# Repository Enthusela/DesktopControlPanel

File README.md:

# The Desktop Control Panel Project

An open-source, hand-built, tactile, home-brew smart-home hub with analog PC audio monitoring and control.

## Features

* ARGB LED device control with HSV and color-temperature control modes
* App-based volume mixing in Windows, including OS/Game/Discord channels
* Motorised knobs enable multiple control modes on a single set of inputs
* Mains power control: Toggle switches control mains power to the PC, monitors, and speakers via rental-safe RF-based remote-control mains outlets.
* Analog audio monitoring: PC soundcard connects to VU meters and IN-9 Nixie Tubes for level and 3-band spectrum monitoring, respectively
* Moog-inspired build quality: wood cabinet, black brushed-aluminium faceplate, big, satisfying switchgear, and actual Moog knobs/rockers because why not.
* "Seamless" E-ink display: White-on-black E-ink panel creates a non-light-emitting display integrated into the non-light-emitting faceplate.
* Integrated website: the website for this Control Panel project is hosted on the Raspberry Pi running inside the Control Panel
* Integration with Home Assistant for ARGB room-lighting via ESP Wifi boards
* Automatic Temperature-based color control: automatically transition room lighting from cool to warm as the sun sets here in Perth, Western Australia.
* Homebrew phone-control app: Home Assistant has this, of course, but this sounded like a good excuse to learn React Native.

<details>
<summary>Feature Development Status Table</summary>

| Feature/Pipeline                      | Order In Pipeline | Sub-function                        | Status |
|:--------------------------------------|:---:|:----------------------------------------------------|:-----|
| Faceplate -> Mega Hardware Pipeline   | 1   | Faceplate Input Hardware                            | Done |
| Faceplate -> Mega Hardware Pipeline   | 2   | Faceplate Input Breakout Board                      | Testing |
| Faceplate -> Mega Hardware Pipeline   | 3   | Mega* Input Shield                                  | Testing |
| Mega -> Raspi Hardware Pipeline       | 1   | USB Connection                                      | Done |
| Raspi -> Uno Hardware Pipeline        | 1   | USB Connection                                      | Done |
| Raspi -> PC Hardware Pipeline         | 1   | Local Wifi Connection                               | Done |
| Input Knob Motorisation               | 1   | Mega Programming - Input Knob Control Modes         | Done |
| Input Knob Motorisation               | 2   | Motor Driver Shield                                 | Done |
| Input Knob Motorisation               | 3   | Shield -> Motor Connection                          | Done | 
| PC ARGB Control                       | 1   | Mega Programming - Input signal processing          | Done |
| PC ARGB Control                       | 2a  | Raspi* Programming - Input passthrough to Uno       | Done |
| PC ARGB Control                       | 2b  | Raspi Programming - Home Assistant/Web App          | Not Started |
| PC ARGB Control                       | 3a  | Uno* Programming - Manual HSV-based Color Control   | Done |
| PC ARGB Control                       | 3b  | Uno Programming - Manual Temp-based Color Control   | Done |
| PC ARGB Control                       | 3c  | Uno Programming - Auto Temp-based Color Control     | Not Started |
| PC ARGB Control                       | 4   | Uno ARGB Breakout Shield                            | To Be Ordered |
| PC ARGB Control                       | 5   | PC ARGB Devices                                     | Done |
| PC Volume Control                     | 1   | Raspi Programming - Input passthrough to PC         | Done |
| PC Volume Control                     | 2a  | PC Programming - Main Volume Control                | Done |
| PC Volume Control                     | 2b  | PC Programming - Three-channel App Volume Control   | Done |
| PC Volume Control                     | 2c  | PC Programming - Audio Output Device Selection      | Done |
| Mains Power Control                   | 1   | Mega Programming - Input Signal Processing          | In progress |
| Mains Power Control                   | 2   | Mega -> RF PCB Breakout Board                       | In progress |
| Mains Power Control                   | 3   | RF PCB -> Remote Mains Outlet Connection            | In progress |
| Mains Power Control                   | 4   | Remote Mains Outlets - Test Working                 | In progress |
| PC Audio Level Meters                 | 1   | Soundcard TRS Output Levels                         | Done |
| PC Audio Level Meters                 | 2a  | Soundcard -> Driver Board Connection                | Done |
| PC Audio Level Meters                 | 2b  | Power Supply -> Driver Board Connection             | Developing |
| PC Audio Level Meters                 | 3   | VU Meter Driver Board                               | Done |
| PC Audio Level Meters                 | 4a  | VU Meter Level Outputs                              | Done |
| PC Audio Level Meters                 | 4b  | VU Meter LED Outputs                                | Done |
| PC Audio Level Meters                 | 5a  | VU Meters                                           | Done |
| PC Audio Level Meters                 | 5b  | VU Meter LEDs                                       | Prototyped |
| PC Audio Spectrum Analyser            | 1   | Soundcard Optical Output Levels                     | Done |
| PC Audio Spectrum Analyser            | 2   | Soundcard -> Digital I/O Board Connection           | Done |
| PC Audio Spectrum Analyser            | 3   | Raspberry Pi Digital Audio I/O Board                | Testing |
| PC Audio Spectrum Analyser            | 4   | Raspberry Pi Digital Audio I/O Processing           | Developing |
| PC Audio Spectrum Analyser            | 5   | Custom Nixie Tube Driver HAT                        | Developing |
| PC Audio Spectrum Analyser            | 6   | Driver HAT -> Nixie Tube Connection                 | Done |
| PC Audio Spectrum Analyser            | 7   | Power Supply to Driver Board                        | Developing |
| e-Ink Display                         | 1   | Raspberry Pi Programming - Image Output             | Developing |
| e-Ink Display                         | 2   | Raspberry Pi HAT                                    | Done |
| e-Ink Display                         | 3   | e-Ink Display                                       | Done |
| Project Website                       | 1   | Proxy Server (nginx)                                | Done |
| Project Website                       | 2   | Domain Hosting                                      | Done |
| Project Website                       | 3   | Server (node.js)                                    | Done |
| Project Website                       | 4a  | Homepage                                            | In progress |
| Project Website                       | 4b  | Brief                                               | In progress |
| Project Website                       | 4c  | Timeline                                            | In progress |
| Project Website                       | 4d  | Parts List                                          | In progress |
| Project Website                       | 4e  | Gallery                                             | In progress |
| Project Website                       | 4f  | Interactive Panel Map                               | Not started |
| Cabinet                               | N/A | Faceplate VU Meter Mounts                           | Done |
| Cabinet                               | N/A | Faceplate Nixie Tube Mounts                         | Done |
| Cabinet                               | N/A | Faceplate Soundcard Mount                           | Done |
| Cabinet                               | N/A | Faceplate e-Ink Display Mount                       | Done |
| Cabinet                               | N/A | Faceplate Input Knobs                               | Done |
| Cabinet                               | N/A | Faceplate Input Knob Motors/Gears                   | Done |
| Cabinet                               | N/A | Faceplate Input Rocker Switches                     | Done |
| Cabinet                               | N/A | Faceplate Input Toggle Switches                     | Done |
| Cabinet                               | N/A | Faceplate Input Push-button Switches                | Done |
| Cabinet                               | N/A | Internal Mounting Plate                             | Done |
| Cabinet                               | N/A | Rear Plate Plate                                    | Done |
| Cabinet                               | N/A | Cabinet Top Plate                                   | Done |
| Cabinet                               | N/A | Cabinet Side Plates                                 | Done |
| Cabinet                               | N/A | Cabinet Bottom Plate                                | In progress |
| Room ARGB Control                     | 1a  | Raspi Programming - Home Assistant Server           | Not started |
| Room ARGB Control                     | 1b  | Raspi Programming - Home Assistant Phone App        | Not started |
| Room ARGB Control                     | 2   | ESP32 Programming - Home Assistant Client           | Not started |
| Room ARGB Control                     | 3   | ESP32 ARGB Breakout Shield                          | Prototyped  |
| Room ARGB Control                     | 4   | Room ARGB Devices - Confirm Working                 | Not started |
| e-Ink Touch Overlay                   | 1   | Touch Overlay                                       | Not started |
| e-Ink Touch Overlay                   | 2   | Touch Overlay -> Raspi Connection                   | Not started |

* "Mega", "Raspi", and "Uno" refer to the Arduino Mega, Raspberry Pi, and Arduino Uno boards used, respectively.

</details>

## Background

This project grew out of a number of frustrations I was having building a killer PC setup that was both functional and aesthetically-pleasing: both important in a 1-by-1 apartment where said PC setup takes up a good third of the available living-room space.

<details>
<summary>ARGB controller software is not pleasant to use</summary>
<br>
The main idea for this project came out of my own frustration with existing hardware/software for controlling ARGB LEDs built into PC components. Most ARGB devices, like fans, must be plugged into a controller that interfaces with software running on the PC. This software is manufacturer-specific, closed-source, and typically quite limited in what it can do: you get some pre-loaded color patterns, but if you want it to do anything else, you're out of luck. To make matters worse, the software is often classic "bloatware": it insists on starting on login, then runs slow, chews up computer resources on functions you didn't ask for, and crashes often. Factor in multiple apps running for different manufacturers, and the user experience gets frustrating fast. While there is some scope to synchronise lighting across different manufacturer's products, these aren't ideal either: I was able to sync my CoolerMaster fans and my Corsair mouse, for instance, but only by using ARGB software tied to my motherboard, which was more limited than the software that came with either product.
</details> 

<details>
<summary>ARGB controller hardware is not special</summary>
<br>
Despite these software problems, I noticed that the physical connections across all my devices was using the same three-pin standard. A quick internet search taught me that the standard was, as expected, a simple Vcc-Data-Gnd pin layout.
</details>

<details>
<summary>Humans did not evolve to relax under rainbow lighting</summary>
<br>
While thinking about making my own ARGB controller, one feature that I particularly wanted was temperature-based color control. I liked the idea of room lighting that could change from cool white during the day to very warm, basically orange, at night. Ideally I'd have my whole apartment lit up like this to make it a well-lit space during the day that gradually becomes softer, warmer, and hopefully more sleep-conducive at night. This is pretty much the antithesis of most pre-built ARGB options, whether that's PC components or ARGB strip-lighting with controllers, which default to "rainbow vomit cyclone". Of course, if I had my own controller then I could make my color-temperature dreams come true.
</details>

<details>
<summary>I like my hardware ~ t e x t u r a l ~</summary>
<br>
I don't know about you, but I really love old-school electronics hardware, particularly audio hardware like synthesisers, amps, mixing tables, etc. The use of materials like wood and metal and glass makes them look and feel so much nicer, so much more hand-crafted, than anything you can get out of molded plastic. All that physical switchgear gives it a sense of weight and purpose; you just know there's a heap of clever analog wizardry going on in there as you move physical components about. It's kind of the opposite of the experience I was getting with the ARGB controllers, which is basically "plug in this small plastic box and hope the software will work". If I was ever going to build my own electronics hardware, something really cool, it would take a lot of design queues from that kind of old-school equipment.
</details>

<details>
<summary>I wanted a new job</summary>
<br>
This project became part of my Master Plan to pivot from Mechatronics Engineer to Software Engineer. If everything so far sounds like something I could have just bought one or more smart-home products to do, then yes, you're right, but as the feature set grew I realised varied tech stack required to build it would make it an ideal showcase project.
</details>

<details>
<summary>The Idea</summary>
<br>
So I have lighting software that doesn't work, connected to hardware that isn't complicated, pushing out colors I don't like, in a form factor that's the opposite of what I like in technology. What if I made the opposite of that? An open-source controller, accepting whatever standard plug-ins my devices used, with all of the color-control options I could think up, built into a sleek bit of hardware that makes you go "Nice." Maybe it'd look a little like this...
<br>

This repo contains (almost) everything I've built so far to make bring that digital finger-painting to life.
</details>

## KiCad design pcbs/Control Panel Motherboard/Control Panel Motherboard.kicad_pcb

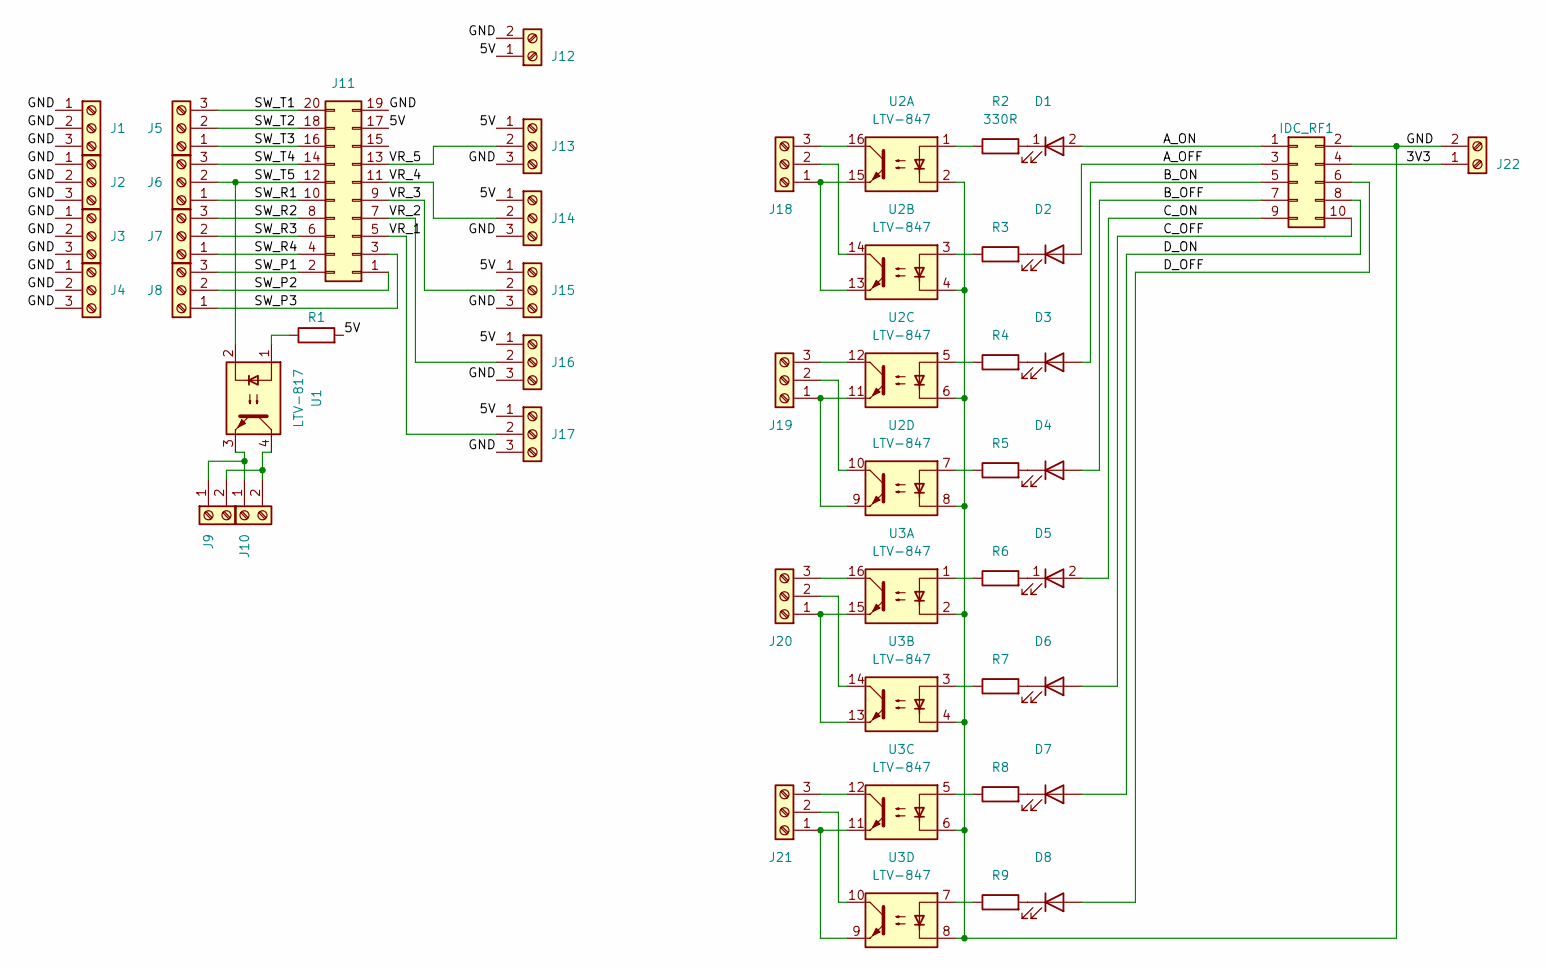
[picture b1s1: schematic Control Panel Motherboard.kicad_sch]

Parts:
D1, D2, D3, D4, D5, D6, D7, D8: LED; LED_D3.0mm
IDC_RF1: IDC_SW; IDC-Header_2x05_P2.54mm_Vertical
J1, J2, J3, J4, J5, J6, J7, J8, J13, J14, J15, J16, J17, J18, J19, J20, J21: Screw_Terminal_01x03; TerminalBlock_bornier-3_P5.08mm
J9, J10, J12, J22: Screw_Terminal_01x02; TerminalBlock_bornier-2_P5.08mm
J11: J_IDC_SW_IN; IDC-Header_2x10_P2.54mm_Vertical
R1, R2, R3, R4, R5, R6, R7, R8, R9: 330R; R_Axial_DIN0207_L6.3mm_D2.5mm_P7.62mm_Horizontal
U1: LTV-817; DIP-4_W7.62mm
U2, U3: LTV-847; DIP-16_W7.62mm

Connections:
/3V3: IDC_RF1.4, J22.1
/5V: J11.17, J12.1, J13.1, J14.1, J15.1, J16.1, J17.1, R1.2
/A_OFF: D2.2 (A), IDC_RF1.3
/A_ON: D1.2 (A), IDC_RF1.1
/B_OFF: D4.2 (A), IDC_RF1.7
/B_ON: D3.2 (A), IDC_RF1.5
/C_OFF: D6.2 (A), IDC_RF1.10
/C_ON: D5.2 (A), IDC_RF1.9
/D_OFF: D8.2 (A), IDC_RF1.6
/D_ON: D7.2 (A), IDC_RF1.8
/GND: IDC_RF1.2, J1.1, J1.2, J1.3, J2.1, J2.2, J2.3, J3.1, J3.2, J3.3, J4.1, J4.2, J4.3, J11.19, J12.2, J13.3, J14.3, J15.3, J16.3, J17.3, J22.2, U2.2, U2.4, U2.6, U2.8, U3.2, U3.4, U3.6, U3.8
/SW_P1: J8.3, J11.2
/SW_P2: J8.2, J11.1
/SW_P3: J8.1, J11.3
/SW_R1: J6.1, J11.10
/SW_R2: J7.3, J11.8
/SW_R3: J7.2, J11.6
/SW_R4: J7.1, J11.4
/SW_T1: J5.3, J11.20
/SW_T2: J5.2, J11.18
/SW_T3: J5.1, J11.16
/SW_T4: J6.3, J11.14
/SW_T5: J6.2, J11.12, U1.2
/VR_1: J11.5, J17.2
/VR_2: J11.7, J16.2
/VR_3: J11.9, J15.2
/VR_4: J11.11, J14.2
/VR_5: J11.13, J13.2
unnamed: D1.1 (K), R2.2
unnamed: D2.1 (K), R3.2
unnamed: D3.1 (K), R4.2
unnamed: D4.1 (K), R5.2
unnamed: D5.1 (K), R6.2
unnamed: D6.1 (K), R7.2
unnamed: D7.1 (K), R8.2
unnamed: D8.1 (K), R9.2
unnamed: J9.1, J10.1, U1.3
unnamed: J9.2, J10.2, U1.4
unnamed: J18.1, U2.13, U2.15
unnamed: J18.2, U2.14
unnamed: J18.3, U2.16
unnamed: J19.1, U2.9, U2.11
unnamed: J19.2, U2.10
unnamed: J19.3, U2.12
unnamed: J20.1, U3.13, U3.15
unnamed: J20.2, U3.14
unnamed: J20.3, U3.16
unnamed: J21.1, U3.9, U3.11
unnamed: J21.2, U3.10
unnamed: J21.3, U3.12
unnamed: R1.1, U1.1
unnamed: R2.1, U2.1
unnamed: R3.1, U2.3
unnamed: R4.1, U2.5
unnamed: R5.1, U2.7
unnamed: R6.1, U3.1
unnamed: R7.1, U3.3
unnamed: R8.1, U3.5
unnamed: R9.1, U3.7

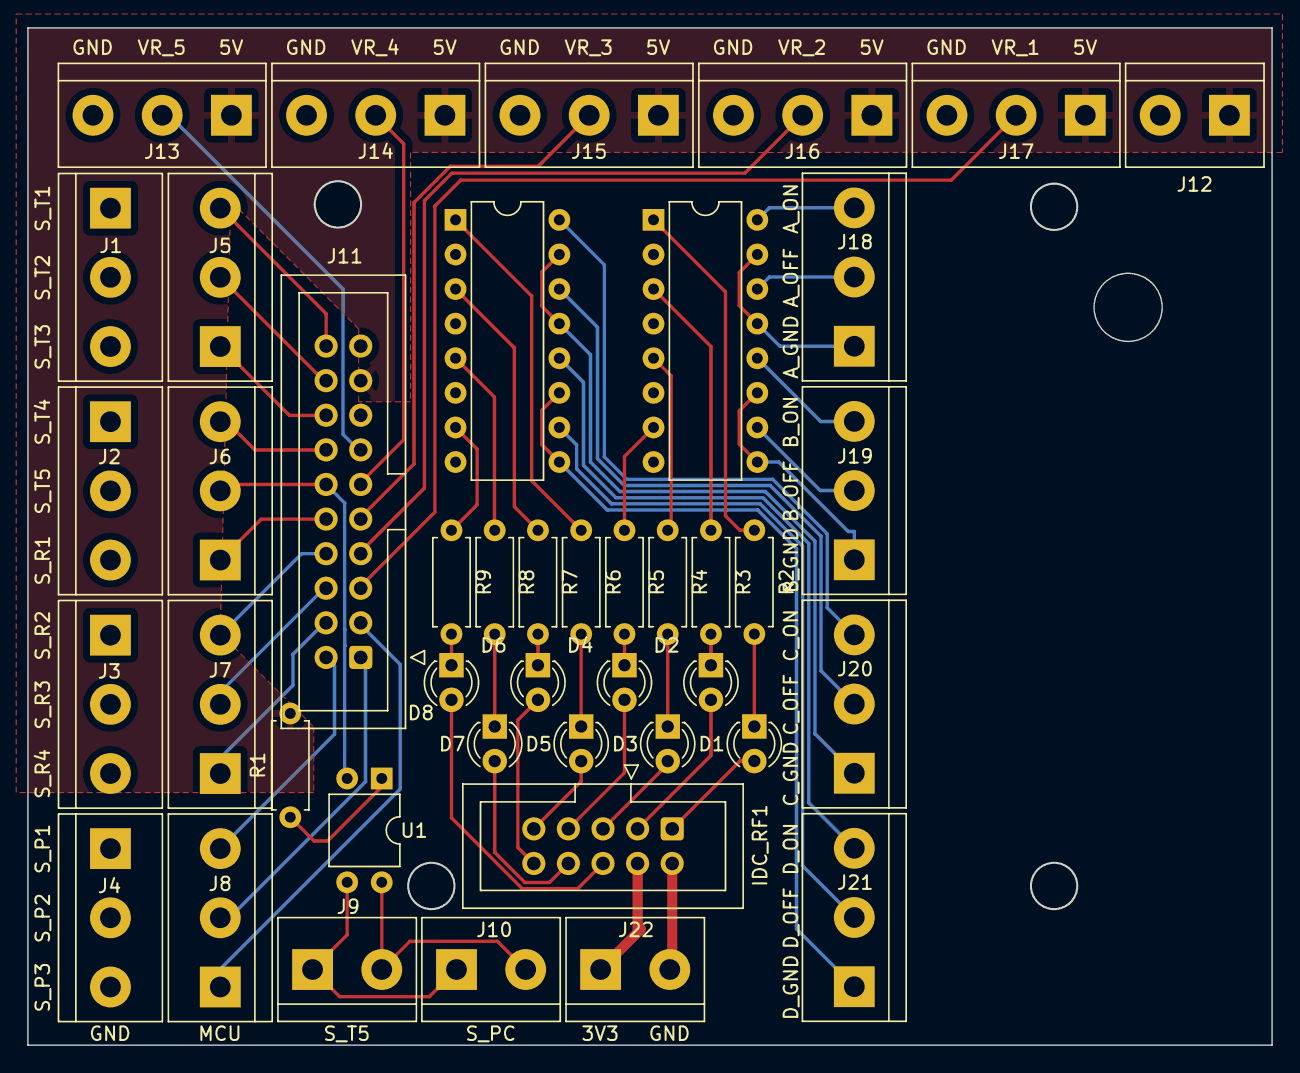
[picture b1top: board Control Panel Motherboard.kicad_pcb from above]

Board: 2 copper layers, 91.3 x 74.7 mm, 43 parts (0 on the bottom side), 59 nets.

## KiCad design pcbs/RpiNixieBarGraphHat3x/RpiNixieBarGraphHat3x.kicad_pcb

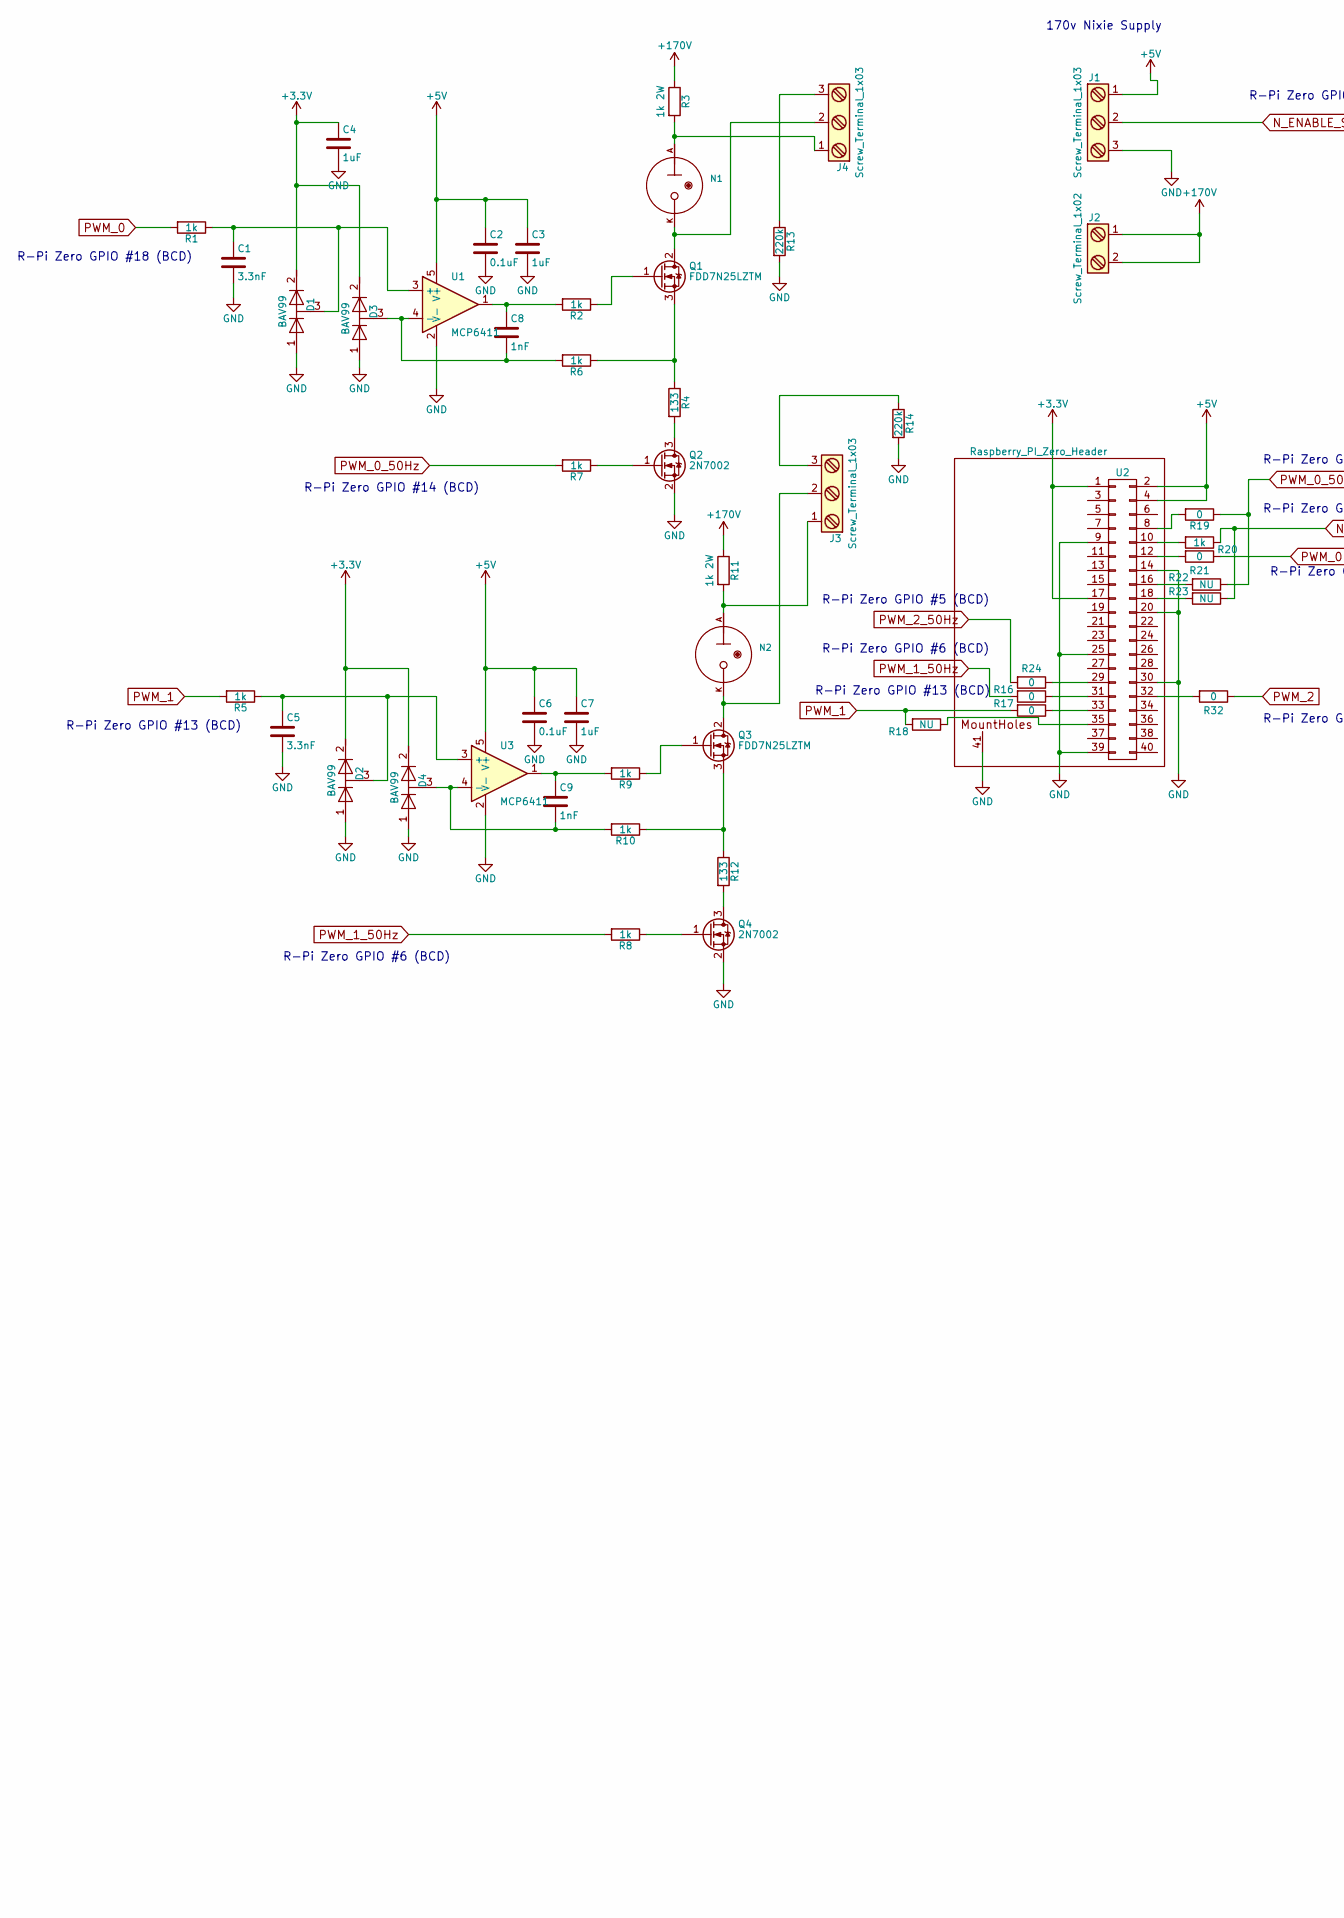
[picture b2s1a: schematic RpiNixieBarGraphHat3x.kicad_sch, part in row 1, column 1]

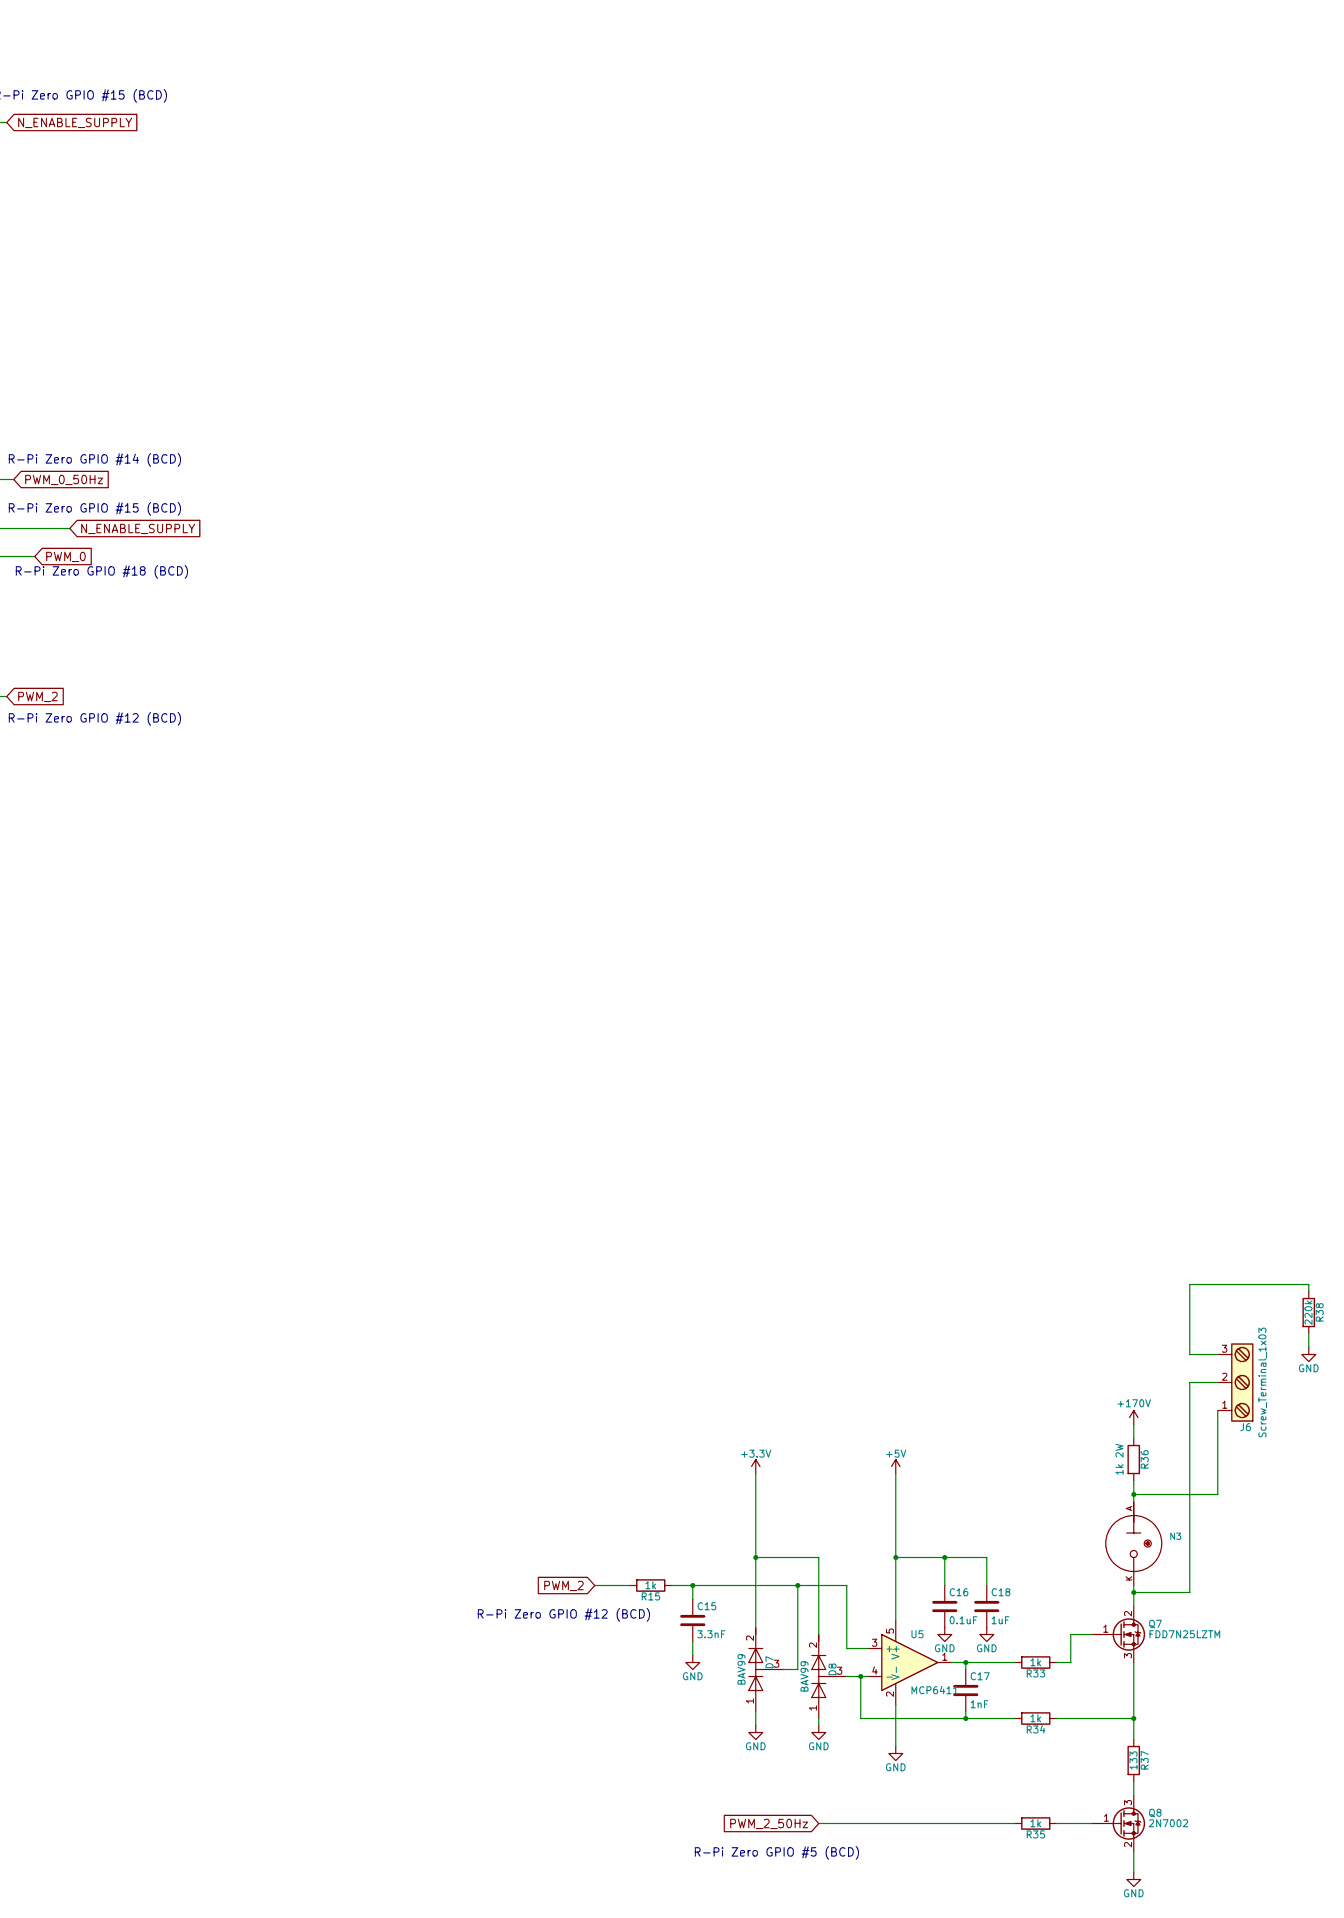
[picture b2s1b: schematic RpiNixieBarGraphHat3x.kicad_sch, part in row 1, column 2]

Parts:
C1, C5, C15: 3.3nF; C_0805_2012Metric_Pad1.18x1.45mm_HandSolder; MPN C0805C332KDRACAUTO
C2, C6, C16: 0.1uF; C_0805_2012Metric_Pad1.18x1.45mm_HandSolder; MPN C0805C104K3RACTU
C3, C4, C7, C18: 1uF; C_0805_2012Metric_Pad1.18x1.45mm_HandSolder; MPN CL21F105ZBFNNNE
C8, C9, C17: 1nF; C_0805_2012Metric_Pad1.18x1.45mm_HandSolder; MPN C0805C102J5HACAUTO
D1, D2, D3, D4, D7, D8: BAV99; SOT-23; MPN BAV99,235
J1, J3, J4, J6: Screw_Terminal_1x03; TerminalBlock_Phoenix_MPT-0,5-3-2.54_1x03_P2.54mm_Horizontal; MPN 1725669
J2: Screw_Terminal_1x02; TerminalBlock_Phoenix_MPT-0,5-3-2.54_1x02_P2.54mm_Horizontal; MPN 1725656
N1, N2, N3: IN-9; nixies-us_IN-9
Q1, Q3, Q7: FDD7N25LZTM; TO-252-2; MPN FDD7N25LZTM
Q2, Q4, Q8: 2N7002; SOT-23; MPN 2N7002-TP
R1, R5, R6, R7, R8, R10, R15, R34, R35: 1k; R_0805_2012Metric_Pad1.20x1.40mm_HandSolder; MPN RC0805FR-071KL
R2, R9, R33: 1k; R_0805_2012Metric_Pad1.20x1.40mm_HandSolder; MPN RC0805FR-078K2L
R3, R11, R36: 1k 2W; R_Axial_DIN0411_L9.9mm_D3.6mm_P12.70mm_Horizontal; MPN PR02000201001JR500
R4, R12, R37: 133; R_0805_2012Metric_Pad1.20x1.40mm_HandSolder; MPN RC0805FR-07133RL
R13, R14, R38: 220k; R_0805_2012Metric_Pad1.20x1.40mm_HandSolder; MPN CRGCQ0805F220K
R16, R17, R19, R21, R24, R32: 0; R_0805_2012Metric_Pad1.20x1.40mm_HandSolder
R18, R22, R23: NU; R_0805_2012Metric_Pad1.20x1.40mm_HandSolder
R20: 1k; R_0805_2012Metric_Pad1.20x1.40mm_HandSolder
U1, U3, U5: MCP6411; SOT-23-5_HandSoldering; MPN MCP6411T-E/OT
U2: Raspberry_PI_Zero_Header; Raspberry_Pi_Zero_40pins

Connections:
+3V3: C4.1, D1.2 (K), D2.2 (K), D3.2 (K), D4.2 (K), D7.2 (K), D8.2 (K), U2.1, U2.17
+5V: C2.1, C3.1, C6.1, C7.1, C16.1, C18.1, J1.1, U1.5 (V+), U2.2, U2.4, U3.5 (V+), U5.5 (V+)
+170V: J2.1, J2.2, R3.1, R11.1, R36.1
GND: C1.2, C2.2, C3.2, C4.2, C5.2, C6.2, C7.2, C15.2, C16.2, C18.2, D1.1 (A), D2.1 (A), D3.1 (A), D4.1 (A), D7.1 (A), D8.1 (A), J1.3, Q2.2 (S), Q4.2 (S), Q8.2 (S), R13.2, R14.2, R38.2, U1.2 (V-), U2.9, U2.14, U2.20, U2.25, U2.30, U2.39, U2.41 (MountHoles), U3.2 (V-), U5.2 (V-)
N_ENABLE_SUPPLY: J1.2, R20.1, R23.1
unnamed: C8.1, R2.2, U1.1
unnamed: C9.1, R9.2, U3.1
unnamed: C17.1, R33.2, U5.1
unnamed: C1.1, D1.3 (common), R1.1, U1.3 (+)
unnamed: C5.1, D2.3 (common), R5.1, U3.3 (+)
unnamed: C8.2, D3.3 (common), R6.2, U1.4 (-)
unnamed: C9.2, D4.3 (common), R10.2, U3.4 (-)
unnamed: C15.1, D7.3 (common), R15.1, U5.3 (+)
unnamed: C17.2, D8.3 (common), R34.2, U5.4 (-)
unnamed: J3.1, N2.A, R11.2
unnamed: J3.3, R14.1
unnamed: J4.1, N1.A, R3.2
unnamed: J4.3, R13.1
unnamed: J6.1, N3.A, R36.2
unnamed: J6.3, R38.1
unnamed: J4.2, N1.K, Q1.2 (D)
unnamed: Q1.1 (G), R2.1
unnamed: Q1.3 (S), R4.1, R6.1
unnamed: Q2.3 (D), R4.2
unnamed: Q2.1 (G), R7.1
unnamed: J3.2, N2.K, Q3.2 (D)
unnamed: Q3.1 (G), R9.1
unnamed: Q3.3 (S), R10.1, R12.1
unnamed: Q4.3 (D), R12.2
unnamed: Q4.1 (G), R8.1
unnamed: J6.2, N3.K, Q7.2 (D)
unnamed: Q7.1 (G), R33.1
unnamed: Q7.3 (S), R34.1, R37.1
unnamed: Q8.3 (D), R37.2
unnamed: Q8.1 (G), R35.1
unnamed: R19.2, U2.8
unnamed: R20.2, U2.10
unnamed: R21.2, U2.12
unnamed: R22.2, U2.16
unnamed: R23.2, U2.18
unnamed: R24.1, U2.29
unnamed: R16.1, U2.31
unnamed: R32.2, U2.32
unnamed: R17.1, U2.33
unnamed: R18.1, U2.35
PWM_0: R1.2, R21.1
PWM_0_50Hz: R7.2, R19.1, R22.1
PWM_1: R5.2, R17.2, R18.2
PWM_1_50Hz: R8.2, R16.2
PWM_2: R15.2, R32.1
PWM_2_50Hz: R24.2, R35.2

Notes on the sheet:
R-Pi Zero GPIO #18 (BCD)
R-Pi Zero GPIO #15 (BCD)
R-Pi Zero GPIO #5 (BCD)
R-Pi Zero GPIO #6 (BCD)
R-Pi Zero GPIO #12 (BCD)
R-Pi Zero GPIO #14 (BCD)
R-Pi Zero GPIO #13 (BCD)
170v Nixie Supply

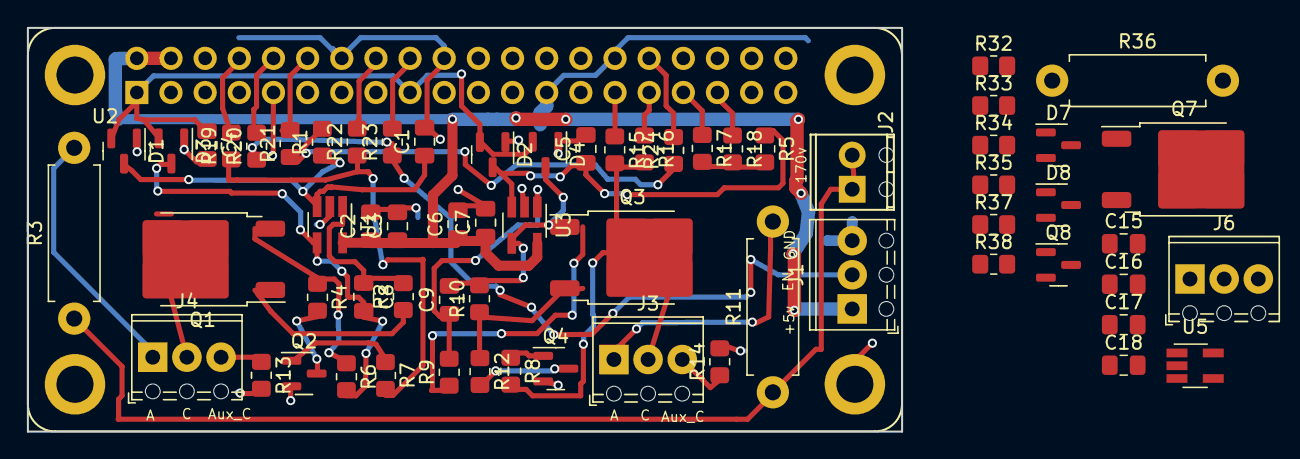
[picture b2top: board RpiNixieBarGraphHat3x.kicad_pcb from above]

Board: 2 copper layers, 65.0 x 30.0 mm, 65 parts (0 on the bottom side), 51 nets.

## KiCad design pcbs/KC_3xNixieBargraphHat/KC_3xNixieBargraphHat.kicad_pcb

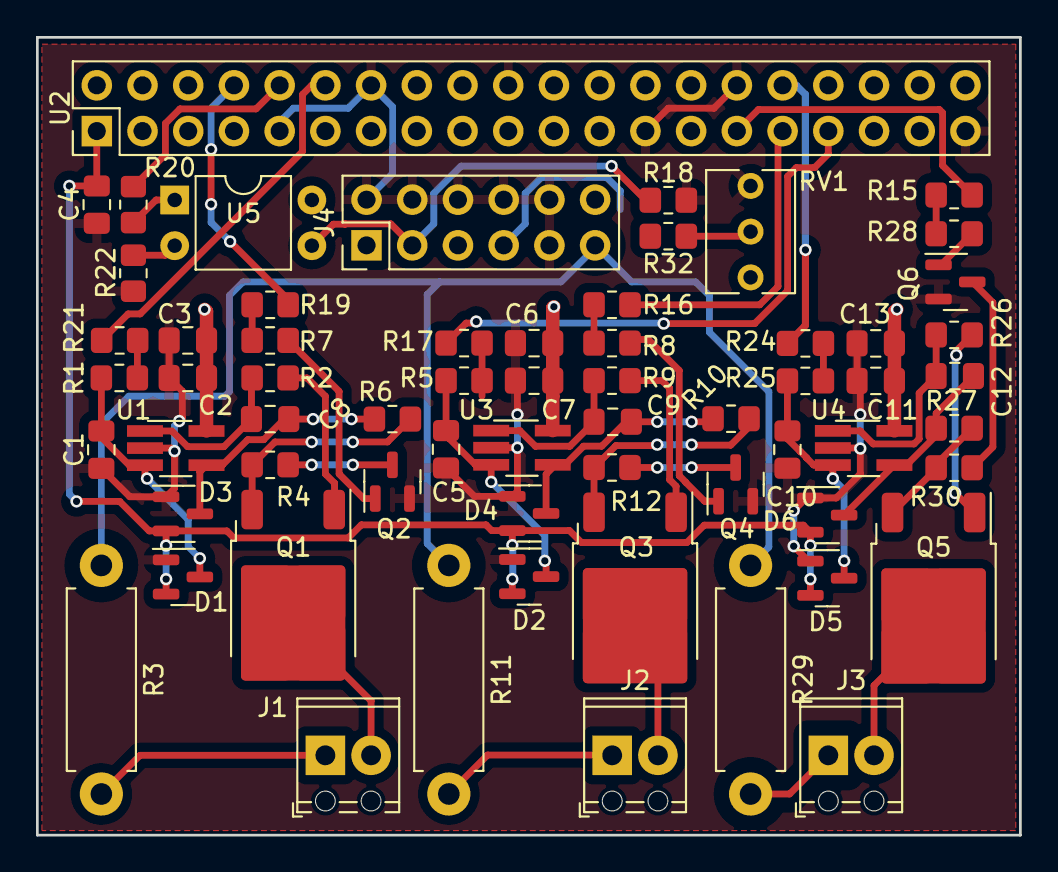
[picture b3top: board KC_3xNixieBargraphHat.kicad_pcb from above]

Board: 2 copper layers, 54.6 x 44.3 mm, 63 parts (0 on the bottom side), 50 nets.

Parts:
C1, C5, C10: 3.3nF; C_0805_2012Metric_Pad1.18x1.45mm_HandSolder
C2, C6, C11: 0.1uF; C_0805_2012Metric_Pad1.18x1.45mm_HandSolder
C3, C4, C7, C13: 1uF; C_0805_2012Metric_Pad1.18x1.45mm_HandSolder
C8, C9, C12: 1nF; C_0805_2012Metric_Pad1.18x1.45mm_HandSolder
D1, D2, D3, D4, D5, D6: BAV99; SOT-23
J1, J2, J3: Screw_Terminal_1x02; TerminalBlock_Phoenix_MPT-0,5-2-2.54_1x02_P2.54mm_Horizontal
J4: Conn_02x06; PinHeader_2x06_P2.54mm_Vertical
Q1, Q3, Q5: FDD7N25LZTM; TO-252-2
Q2, Q4, Q6: 2N7002; SOT-23
R1, R2, R5, R6, R7, R8, R9, R10, R20, R25, R26, R27, R28: 1k; R_0805_2012Metric_Pad1.20x1.40mm_HandSolder
R3, R11, R29: 1k 2W; R_Axial_DIN0411_L9.9mm_D3.6mm_P12.70mm_Horizontal
R4, R12, R30: 133; R_0805_2012Metric_Pad1.20x1.40mm_HandSolder
R15, R16, R17, R19, R21, R24: 0; R_0805_2012Metric_Pad1.20x1.40mm_HandSolder
R18: 100k; R_0805_2012Metric_Pad1.20x1.40mm_HandSolder
R22: 330; R_0805_2012Metric_Pad1.20x1.40mm_HandSolder
R32: 47k; R_0805_2012Metric_Pad1.20x1.40mm_HandSolder
RV1: 5k; Potentiometer_Vishay_T73XW_Horizontal
U1, U3, U4: MCP6411; TSOT-23-5_HandSoldering
U2: Raspberry_PI_Zero_Header; PinHeader_2x20_P2.54mm_Vertical
U5: LTV-817; DIP-4_W7.62mm

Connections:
+3V3: C4.1, D1.2 (K), D2.2 (K), D3.2 (K), D4.2 (K), D5.2 (K), D6.2 (K), U2.1, U2.17
+5V: C2.1, C3.1, C6.1, C7.1, C11.1, C13.1, J4.1, U1.5 (V+), U2.2, U2.4, U3.5 (V+), U4.5 (V+), U5.4
+170V: J4.11, R3.1, R11.1, R29.1
/ENABLE: J4.3, R18.2, U5.3
/N/C: J4.5, J4.12
/R_ADJUST: J4.7, R32.2
GND: C1.2, C2.2, C3.2, C4.2, C5.2, C6.2, C7.2, C10.2, C11.2, C13.2, D1.1 (A), D2.1 (A), D3.1 (A), D4.1 (A), D5.1 (A), D6.1 (A), J4.2, J4.4, J4.6, J4.8, J4.9, J4.10, Q2.2 (S), Q4.2 (S), Q6.2 (S), R18.1, R22.2, RV1.1, U1.2 (V-), U2.9, U2.14, U2.20, U2.25, U2.30, U2.39, U3.2 (V-), U4.2 (V-)
N_ENABLE_SUPPLY: R20.1, U5.1
unnamed: C8.1, R2.2, U1.1
unnamed: C9.1, R9.2, U3.1
unnamed: C12.1, R26.2, U4.1
unnamed: C1.1, D1.3 (common), R1.1, U1.3 (+)
unnamed: C5.1, D2.3 (common), R5.1, U3.3 (+)
unnamed: C8.2, D3.3 (common), R6.2, U1.4 (-)
unnamed: C9.2, D4.3 (common), R10.2, U3.4 (-)
unnamed: C10.1, D5.3 (common), R25.1, U4.3 (+)
unnamed: C12.2, D6.3 (common), R27.2, U4.4 (-)
unnamed: J1.1, R3.2
unnamed: J2.1, R11.2
unnamed: J3.1, R29.2
unnamed: J1.2, Q1.2 (D)
unnamed: Q1.1 (G), R2.1
unnamed: Q1.3 (S), R4.1, R6.1
unnamed: Q2.3 (D), R4.2
unnamed: Q2.1 (G), R7.1
unnamed: J2.2, Q3.2 (D)
unnamed: Q3.1 (G), R9.1
unnamed: Q3.3 (S), R10.1, R12.1
unnamed: Q4.3 (D), R12.2
unnamed: Q4.1 (G), R8.1
unnamed: J3.2, Q5.2 (D)
unnamed: Q5.1 (G), R26.1
unnamed: Q5.3 (S), R27.1, R30.1
unnamed: Q6.3 (D), R30.2
unnamed: Q6.1 (G), R28.1
unnamed: R22.1, U5.2
unnamed: R32.1, RV1.2
unnamed: R19.2, U2.8
unnamed: R20.2, U2.10
unnamed: R21.1, U2.12
unnamed: R15.1, U2.29
unnamed: R16.1, U2.31
unnamed: R24.2, U2.32
unnamed: R17.1, U2.33
PWM_0: R1.2, R21.2
PWM_0_50Hz: R7.2, R19.1
PWM_1: R5.2, R17.2
PWM_1_50Hz: R8.2, R16.2
PWM_2: R24.1, R25.2
PWM_2_50Hz: R15.2, R28.2

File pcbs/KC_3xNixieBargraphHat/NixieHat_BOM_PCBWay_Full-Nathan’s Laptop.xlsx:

|  |  | xxxx xxxx xxxxx xxPCS BOM
 |  |  |  |  |  | 30
Item # | *Designator | *Qty | Manufacturer | *Mfg Part # | Description / Value | *Package/Footprint | Type | Your Instructions / Notes
1 | C1, C5, C10 | 3 | Kemet | C0805C332J4HACTU | 3.3nF | Capacitor_SMD:C_0805_2012Metric_Pad1.18x1.45mm_HandSolder | SMD | Found at: https://www.xonelec.com/mpn/kemet/c0805c332j4hactu
2 | C2, C6, C11 | 3 | Kemet | C0805C104J8RACTU | 0.1uF | Capacitor_SMD:C_0805_2012Metric_Pad1.18x1.45mm_HandSolder | SMD | Found at: https://www.xonelec.com/mpn/kemet/c0805c104j8ractu
3 | C3, C4, C7, C13 | 4 | Kemet | C0805C105J4RACTU | 1uF | Capacitor_SMD:C_0805_2012Metric_Pad1.18x1.45mm_HandSolder | SMD | Found at: https://www.xonelec.com/mpn/kemet/c0805c105j4ractu
4 | C8, C9, C12 | 3 | Kemet | C0805C102J4GACTU | 1nF | Capacitor_SMD:C_0805_2012Metric_Pad1.18x1.45mm_HandSolder | SMD | Found at: https://www.xonelec.com/mpn/kemet/c0805c102j4gactu
5 | D1-D6 | 6 | Nexperia USA Inc. | BAV99,215 | BAV99 | Package_TO_SOT_SMD:SOT-23 | SMD | Found at: https://www.pcbway.com/components/detail/BAV99215/340224/
6 | J1-J3 | 3 | Molex | 0397730002 | Screw_Terminal_1x02 | TerminalBlock_Phoenix:TerminalBlock_Phoenix_MPT-0,5-2-2.54_1x02_P2.54mm_Horizon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 | PTH | Found at: https://www.pcbway.com/components/detail/0397730002/883047/
7 | Q1, Q3, Q5 | 3 | ON Semiconductor | FDD7N25LZTM | FDD7N25LZTM | Package_TO_SOT_SMD:TO-252-2 | SMD | Found at: https://www.xonelec.com/mpn/onsemiconductor/fdd7n25lztm
8 | Q2, Q4, Q6 | 3 | Micro Commercial Components (MCC) | 2N7002-TP | 2N7002 | Package_TO_SOT_SMD:SOT-23 | SMD | Found at: https://www.xonelec.com/mpn/microcommercialcomponentsmcc/2n7002tp
9 | R1, R2, R5-R10, R20, R25-R28 | 13 | Yageo | RT0805FRE071KL | 1k | Resistor_SMD:R_0805_2012Metric_Pad1.20x1.40mm_HandSolder | SMD
10 | R3, R11, R29 | 3 | Vishay | PR02000201001FR500 | 1k 2W | Resistor_THT:R_Axial_DIN0411_L9.9mm_D3.6mm_P12.70mm_Horizontal | PTH
11 | R4, R12, R22, R30 | 3 | Yageo | RT0805FRE07130RL | 133 | Resistor_SMD:R_0805_2012Metric_Pad1.15x1.40mm_HandSolder | SMD
12 | R18 | 1 | Yageo | RT0805FRE07100KL | 100k | Resistor_SMD:R_0805_2012Metric_Pad1.20x1.40mm_HandSolder | SMD
13 | R32 | 1 | Yageo | RT0805FRE0747KL | 47k | Resistor_SMD:R_0805_2012Metric_Pad1.20x1.40mm_HandSolder | SMD
14 | U1, U3, U4 | 3 | Microchip | MCP6411T-E/OT | MCP6411 | Package_TO_SOT_SMD:TSOT-23-5_HandSoldering | SMD | Found at: https://www.xonelec.com/mpn/microchip/mcp6411teot
15 | U5 | 1 | Lite-on | LTV-817-A | LTV-817 | Package_DIP:DIP-4_W7.62mm | PTH
Need a quick and accurante quote? Need an efficient production? Please read SMT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
Click for Instructions on How to Create a BOM

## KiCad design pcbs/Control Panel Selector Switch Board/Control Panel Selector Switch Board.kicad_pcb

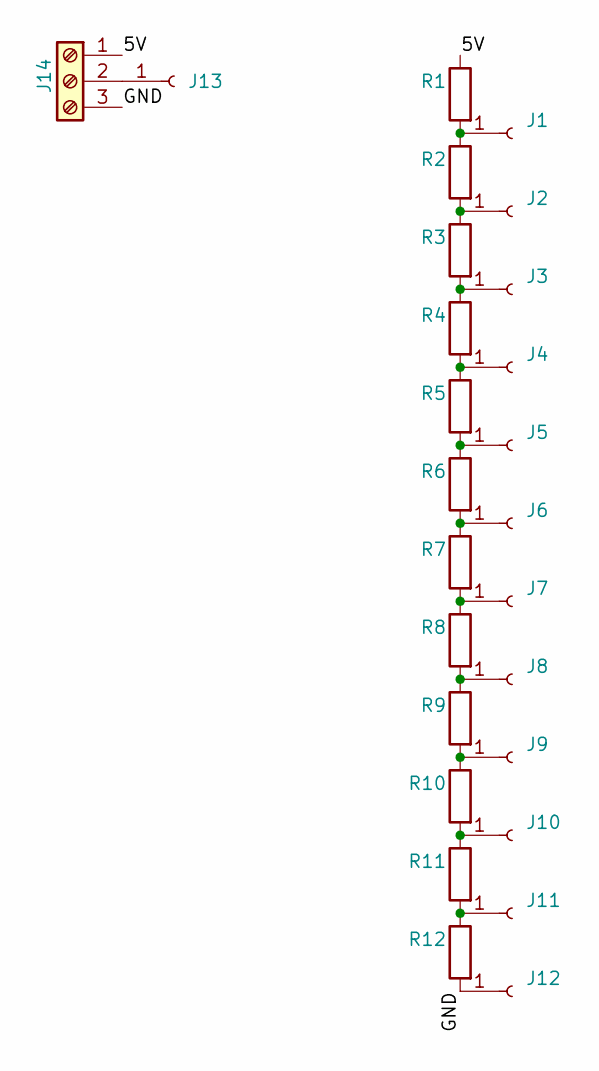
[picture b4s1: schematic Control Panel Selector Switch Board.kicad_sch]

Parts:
J1, J2, J3, J4, J5, J6, J7, J8, J9, J10, J11, J12, J13: Conn_01x01_Female; Pin_D1.0mm_L10.0mm
J14: Screw_Terminal_01x03; TerminalBlock_bornier-3_P5.08mm
R1, R2, R3, R4, R5, R6, R7, R8, R9, R10, R11, R12: 330R; R_Axial_DIN0204_L3.6mm_D1.6mm_P5.08mm_Horizontal

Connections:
/5V: J14.1, R1.1
/GND: J12.1, J14.3, R12.2
unnamed: J1.1, R1.2, R2.1
unnamed: J2.1, R2.2, R3.1
unnamed: J3.1, R3.2, R4.1
unnamed: J4.1, R4.2, R5.1
unnamed: J5.1, R5.2, R6.1
unnamed: J6.1, R6.2, R7.1
unnamed: J7.1, R7.2, R8.1
unnamed: J8.1, R8.2, R9.1
unnamed: J9.1, R9.2, R10.1
unnamed: J10.1, R10.2, R11.1
unnamed: J11.1, R11.2, R12.1
unnamed: J13.1, J14.2

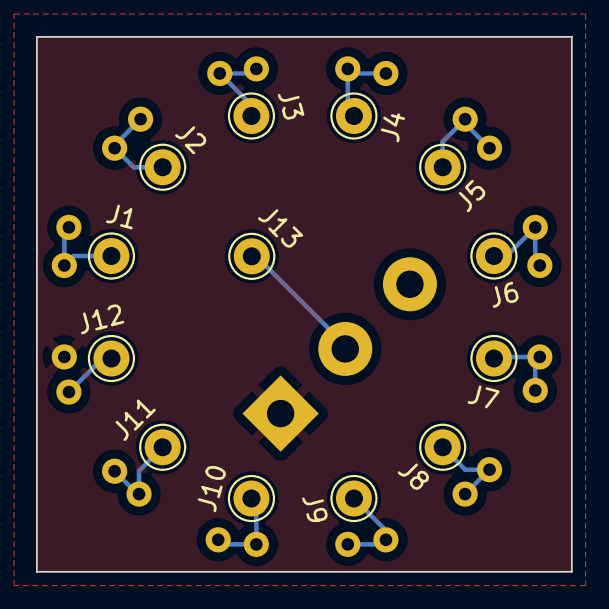
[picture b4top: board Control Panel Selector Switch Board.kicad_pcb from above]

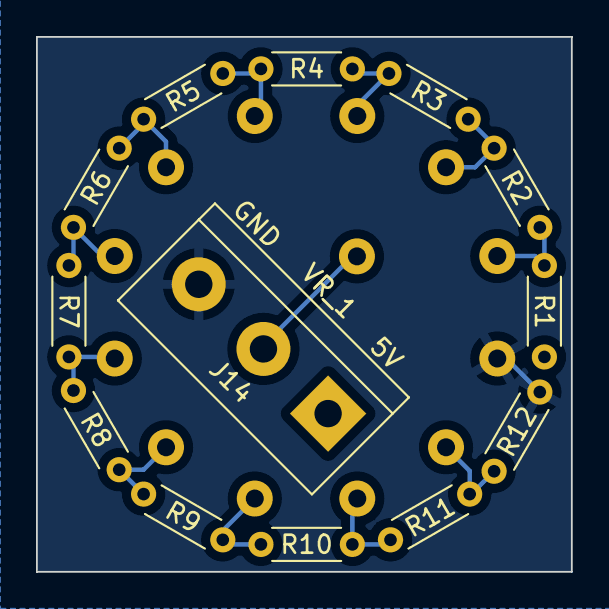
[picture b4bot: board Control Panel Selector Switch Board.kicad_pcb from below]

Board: 2 copper layers, 29.7 x 29.7 mm, 26 parts (13 on the bottom side), 14 nets.
